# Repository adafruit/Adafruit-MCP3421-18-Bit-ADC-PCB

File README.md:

## Adafruit MCP3421 18-Bit ADC - STEMMA QT / Qwiic PCB

<a href="http://www.adafruit.com/products/5870"><br/>
Click here to purchase one from the Adafruit shop</a>

PCB files for the Adafruit MCP3421 18-Bit ADC - STEMMA QT / Qwiic. 

Format is EagleCAD schematic and board layout
* https://www.adafruit.com/product/5870

### Description

The Adafruit MCP3421 18-Bit ADC is a simple, inexpensive, and easy to use 18-bit, 240 SPS, single-channel ADC with an I2C interface that can run up to 3.4MHz clock rate. A perfect component whenever you need an ADC that has differential inputs, adjustable gain, and a built in precision/low-drift reference voltage.

One of the trade-offs with getting 18-bit precision is that the ADC is not going to be very fast: you can configure the chip to do a faster 12-bit conversion at 240 SPS, but at 18-bits it slows down to 3.5 SPS.
That's because the way a sigma-delta ADC works, it 'guesses' the analog voltage and uses a comparator to determine whether the input is higher or lower. Each 'guess' takes an extra step, and thus
halves the throughput, so 12-bit is 240 SPS, and 14-bit is 1/4 (2-bit) slower, 60 SPS. Ditto 16-bit is 1/4 slower, 15 SPS, and finally 18-bit is 3.75 SPS.

The MCP3421 is already set up for differential inputs, which means that you can read positive or negative differences between the two inputs, as long as both signals are between 0 and 2.048V. This means its not going to be great for reading stuff like potentiometers, where you have a single-end reading referenced to ground, and you want to read the full range from 0 to Vcc. It is great, however, for reading sensors like strain gauges, pressure sensors, or thermocouples.

We have a ready to go Arduino library that makes usage simple: select the sample rate / precision you want and one-shot or continuous mode. Then read values over I2C! This sensor has a fixed address, so you may want to use a multiplexor if you want to connect multiple MCP3421's on a single I2C bus.

To get you going fast, we spun up a custom-made PCB in the STEMMA QT form factor, making it easy to interface with. The STEMMA QT connectors on either side are compatible with the SparkFun Qwiic I2C connectors. This allows you to make solderless connections between your development board and the MCP or to chain it with a wide range of other sensors and accessories using a compatible cable.

QT Cable is not included, but we have a variety in the shop.

Comes with a bit of 0.1" standard header in case you want to use it with a breadboard or perfboard. Four mounting holes for easy attachment.

### License

Adafruit invests time and resources providing this open source design, please support Adafruit and open-source hardware by purchasing products from [Adafruit](https://www.adafruit.com)!

Designed by Limor Fried/Ladyada for Adafruit Industries.

Creative Commons Attribution/Share-Alike, all text above must be included in any redistribution. 
See license.txt for additional details.

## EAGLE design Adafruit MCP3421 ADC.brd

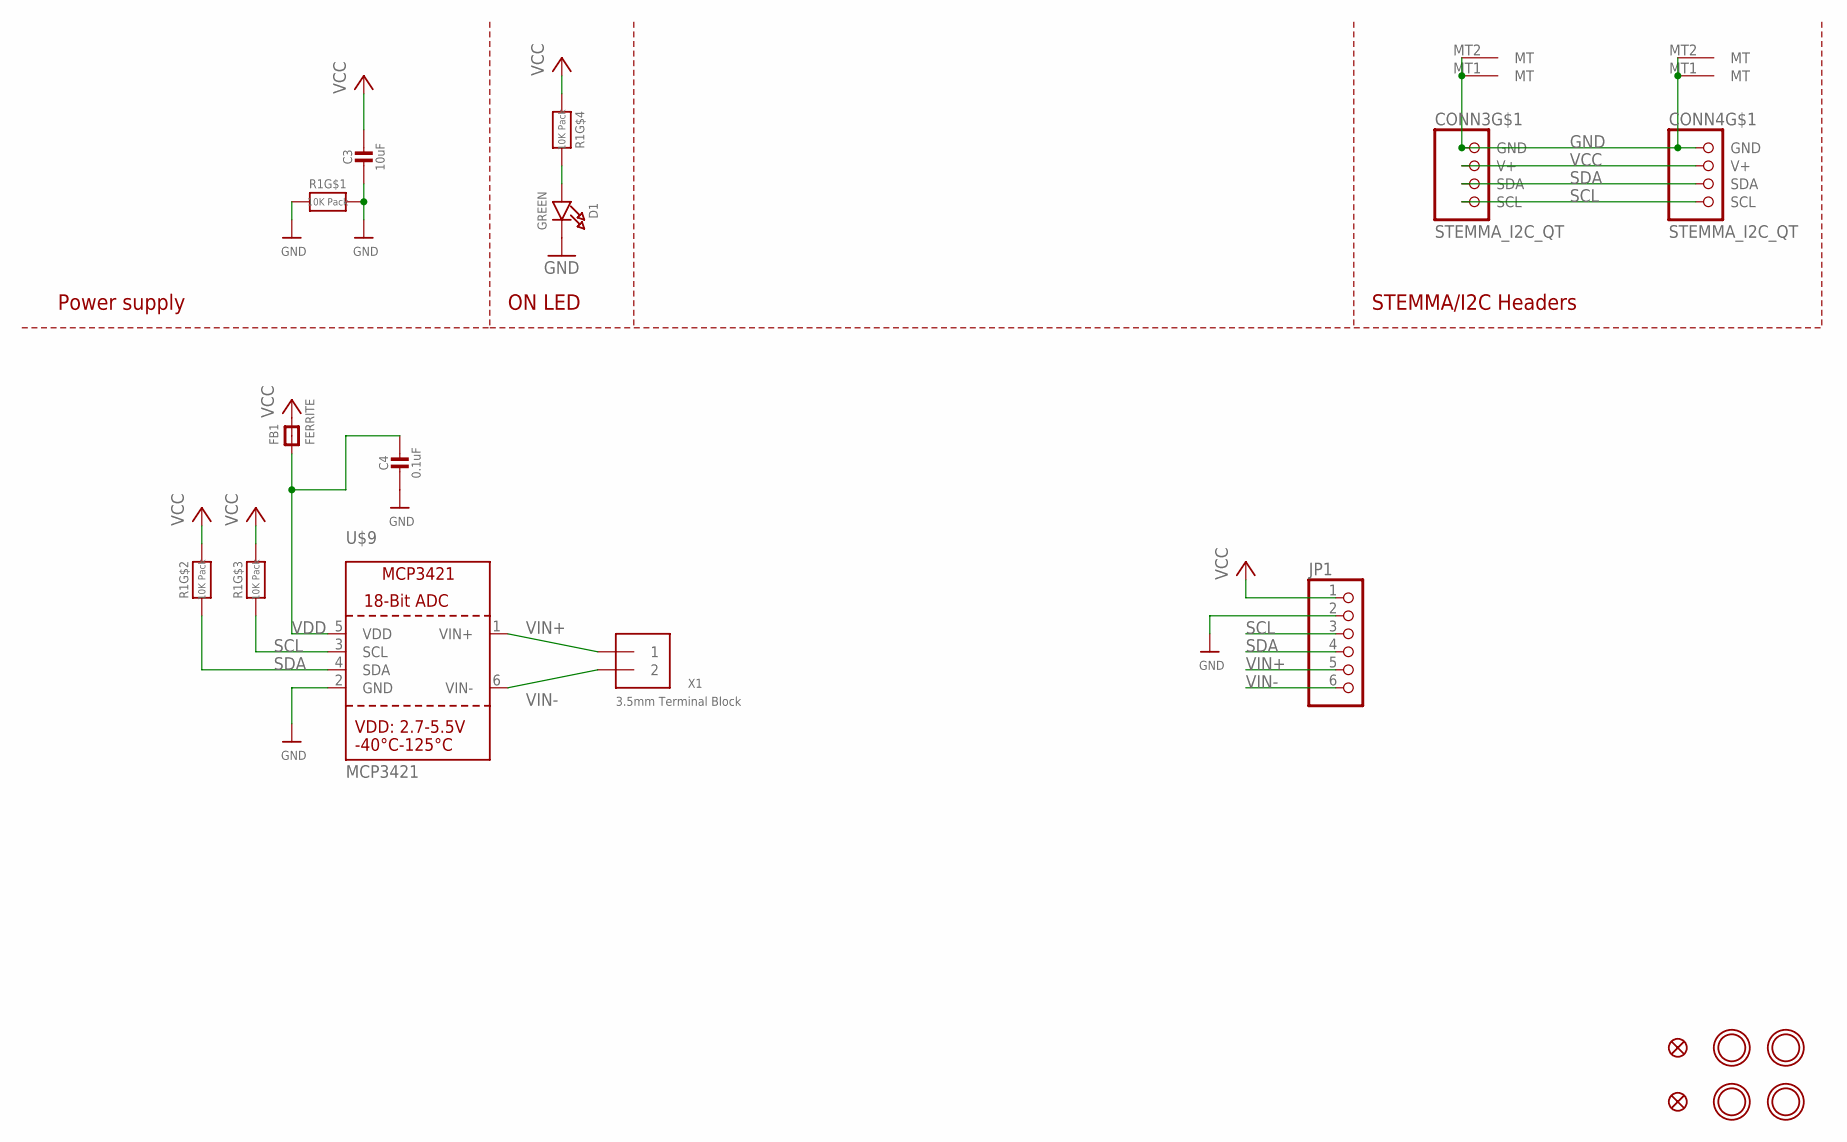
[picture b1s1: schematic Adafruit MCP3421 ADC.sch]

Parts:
C3: 10uF; 0805-NO
C4: 0.1uF; 0603-NO
CONN3, CONN4: STEMMA_I2C_QT; JST_SH4
D1: GREEN; CHIPLED_0603_NOOUTLINE
FB1: FERRITE; 0603-NO
FID3, FID4: FIDUCIAL_1MM
JP1: HEADER-1X670MIL; 1X06_ROUND_70
R1: 10K Pack; RESPACK_4X0603
U$9: MCP3421; SOT23-6
U$20, U$21, U$25, U$27: MOUNTINGHOLE2.5; MOUNTINGHOLE_2.5_PLATED
X1: 3.5mm Terminal Block; TERMBLOCK_1X2-3.5MM

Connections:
GND: C3.2, C4.2, CONN3.1 (GND), CONN3.MT1 (MT), CONN3.MT2 (MT), CONN4.1 (GND), CONN4.MT1 (MT), CONN4.MT2 (MT), D1.C, JP1.2, R1.1, R1.8 (2), U$9.2 (GND)
unnamed: D1.A, R1.5 (2)
SCL: CONN3.4 (SCL), CONN4.4 (SCL), JP1.3, R1.3 (1), U$9.3 (SCL)
SDA: CONN3.3 (SDA), CONN4.3 (SDA), JP1.4, R1.2 (1), U$9.4 (SDA)
VCC: C3.1, CONN3.2 (V+), CONN4.2 (V+), FB1.2, JP1.1, R1.4 (1), R1.6 (2), R1.7 (2)
VDD: C4.1, FB1.1, U$9.5 (VDD)
VIN+: JP1.5, U$9.1 (VIN+), X1.1
VIN-: JP1.6, U$9.6 (VIN-), X1.2

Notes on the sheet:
STEMMA/I2C Headers
ON LED
Power supply

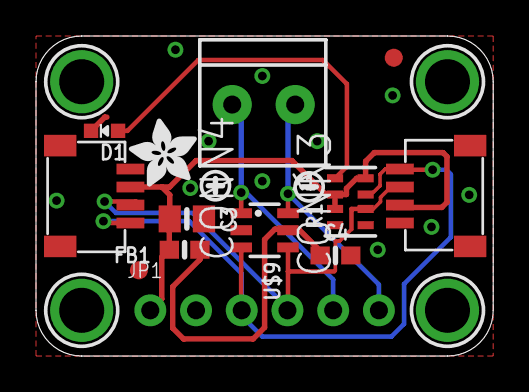
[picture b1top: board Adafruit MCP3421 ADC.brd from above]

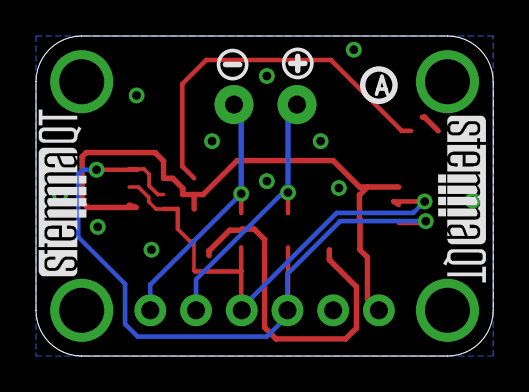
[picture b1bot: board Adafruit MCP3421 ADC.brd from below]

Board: 2 copper layers, 25.4 x 17.8 mm, 37 parts (9 on the bottom side), 8 nets.

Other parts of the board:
PLABEL0: PLABEL0
PLABEL1: PLABEL1
PLABEL2: PLABEL2
PLABEL3: PLABEL3
PLABEL4: PLABEL4
PLABEL5: PLABEL5
PLABEL6: PLABEL6
PLABEL7: PLABEL7
PLABEL8: PLABEL8
PLABEL9: PLABEL9
PLABEL10: PLABEL10
PLABEL11: PLABEL11
PLABEL12: PLABEL12
U$2, U$7: SYMBOL_PLUS
U$4, U$5: SYMBOL_MINUS
U$8: PCBFEAT-REV-040
U$29: ADAFRUIT_3.5MM
U$31, U$32: STEMMAQT

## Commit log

2023-12-21 cookiecutter
